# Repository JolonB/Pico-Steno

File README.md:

# Pico-Steno

An open-source Raspberry Pi Pico stenography keyboard.

I promise I'll write more here soon.

Gerber files can be found [here](hardware/gerber/).
I have not yet ordered a PCB with these gerber files, so they may have issues.

The bill of materials can be found [here](docs/bom/).

## Setup

### Flashing Pico

<!-- TODO add instructions for flashing the circuitpython firmware -->

To begin, you need to have `circup` installed so you can add libraries to your Pico.
Start by installing the dependencies:

```shell
sudo apt install -y git python3 python3-pip
```

And then install `circup`:

```shell
pip3 install --upgrade pip
pip3 install circup
```

You can update `circup` by running:

```shell
pip3 install --upgrade circup
```

Now, you can simply install the packages by plugging in your Pico which is running CircuitPython and running:

```shell
cd src/
circup install -r requirements.txt
```

### Compiling Code

To compile the code, you need `mpy-cross` installed on your PC.
You can download it from [here](https://adafruit-circuit-python.s3.amazonaws.com/index.html?prefix=bin/mpy-cross/) and download the latest version for your operating system (or look [here](https://learn.adafruit.com/welcome-to-circuitpython/frequently-asked-questions#how-can-i-create-my-own-mpy-files-3020687-11) if the link is dead).

<!-- TODO add more notes here
Probably only need to compile the custom code, not the libraries. Might as well use circup (https://learn.adafruit.com/keep-your-circuitpython-libraries-on-devices-up-to-date-with-circup/prepare)
Later, could add an explanation for how to build a whole circuit python firmware with custom lib?? -->

### Loading .mpy files onto Pico

## Questions

### Why doesn't this use a keyboard matrix?

Good question.

1. The RPi Pico has enough GPIO pins to dedicate one to each key on a stenography keyboard.
Basically, I just though that was neat, so decided to do it that way.
I then decided I wanted optional extra keys, so added the IO extender.
1. This allows me to implement n-key rollover without needing any diodes; not that they are particularly expensive.

### Why is the circuit so messy?

That's what happens when each key is connected directly to the microcontroller without optimising the which switch connects to which pin.  
But hey, this is open source; if it bugs you, feel free to fork it!

## I can't detect my board

```shell
pip3 install adafruit-board-toolkit
python3 -c "import adafruit_board_toolkit.circuitpython_serial; print(adafruit_board_toolkit.circuitpython_serial.data_comports()[0].device)"
```

If you get `IndexError: tuple index out of range`, then no data port was detected.

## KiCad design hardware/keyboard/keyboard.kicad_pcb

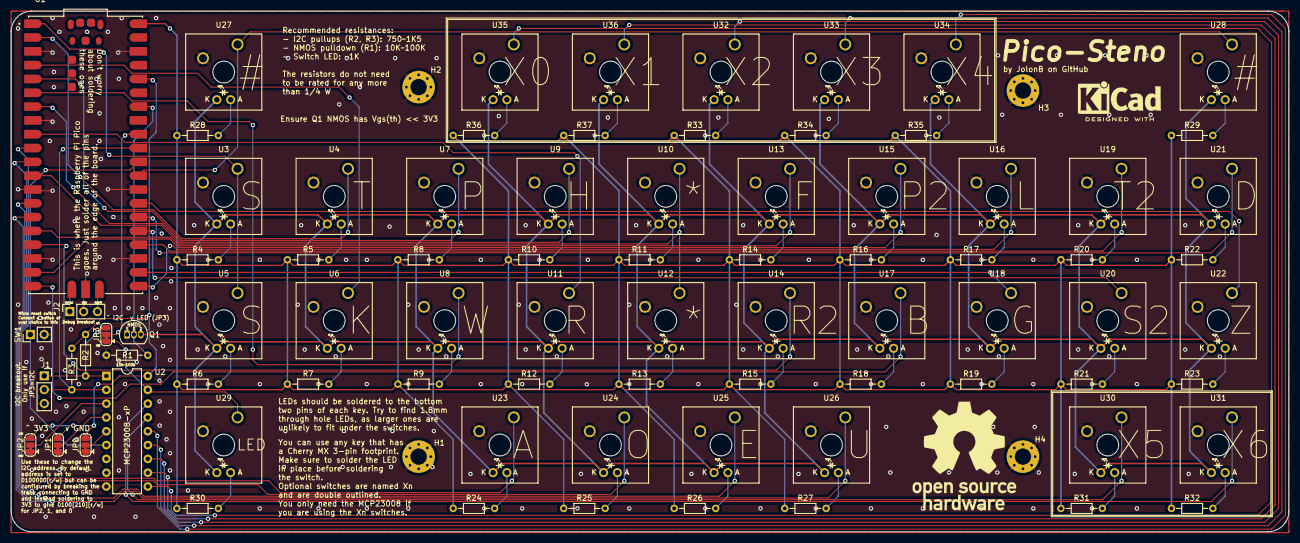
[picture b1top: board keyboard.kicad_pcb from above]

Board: 2 copper layers, 234.9 x 95.7 mm, 85 parts (0 on the bottom side), 79 nets.

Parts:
H1, H2, H3, H4: MountingHole_Pad; MountingHole_3mm_Pad_Via
J1, J2: Conn_01x03_Female; PinSocket_1x03_P2.54mm_Vertical
JP0, JP1, JP2, JP3: SolderJumper_3_Bridged12; SolderJumper-3_P1.3mm_Bridged12_RoundedPad1.0x1.5mm
Q1: Q_NMOS_SGD; TO-92L_Inline
R1, R2, R3, R4, R5, R6, R7, R8, R9, R10, R11, R12, R13, R14, R15, R16, R17, R18, R19, R20, R21, R22, R23, R24, R25, R26, R27, R28, R29, R30, R31, R32, R33, R34, R35, R36, R37: R; R_Axial_DIN0204_L3.6mm_D1.6mm_P7.62mm_Horizontal
SW1: SW_Push; PinHeader_1x02_P2.54mm_Vertical
U1: SC0915; MODULE_SC0915
U2: MCP23008-xP; DIP-18_W7.62mm
U3, U4, U5, U6, U7, U8, U9, U10, U11, U12, U13, U14, U15, U16, U17, U18, U19, U20, U21, U22, U23, U24, U25, U26, U27, U28, U29, U30, U31, U32, U33, U34, U35, U36: CherryMX_LED; CherryMX_1.00u_LED

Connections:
+3V3: JP0.3 (B), JP1.3 (B), JP2.3 (B), R2.1, R3.1, U1.36 (3V3_OUT), U2.18 (VDD)
+5V: R4.1, R5.1, R6.1, R7.1, R8.1, R9.1, R10.1, R11.1, R12.1, R13.1, R14.1, R15.1, R16.1, R17.1, R18.1, R19.1, R20.1, R21.1, R22.1, R23.1, R24.1, R25.1, R26.1, R27.1, R28.1, R29.1, R30.1, R31.1, R32.1, R33.1, R34.1, R35.1, R36.1, R37.1, U1.40 (VBUS)
/I2C_SCL: J1.1, JP3.3 (B), R2.2, U2.1 (SCL)
/I2C_SDA: J1.2, R3.2, U1.31 (GP26), U2.2 (SDA)
/IO_A0: JP0.2 (C), U2.5 (A0)
/IO_A1: JP1.2 (C), U2.4 (A1)
/IO_A2: JP2.2 (C), U2.3 (A2)
/KEY_A: U1.10 (GP7), U23.2
/KEY_B: U1.20 (GP15), U17.2
/KEY_D: U1.26 (GP20), U21.2
/KEY_E: U1.14 (GP10), U25.2
/KEY_EXT0: U2.10 (GP0), U35.2
/KEY_EXT1: U2.11 (GP1), U36.2
/KEY_EXT2: U2.12 (GP2), U32.2
/KEY_EXT3: U2.13 (GP3), U33.2
/KEY_EXT4: U2.14 (GP4), U34.2
/KEY_EXT5: U2.15 (GP5), U30.2
/KEY_EXT6: U2.16 (GP6), U31.2
/KEY_F: U1.16 (GP12), U13.2
/KEY_G: U1.22 (GP17), U18.2
/KEY_H: U1.7 (GP5), U9.2
/KEY_K: U1.4 (GP2), U6.2
/KEY_L: U1.21 (GP16), U16.2
/KEY_NUM: U1.29 (GP22), U27.2, U28.2
/KEY_O: U1.11 (GP8), U24.2
/KEY_P: U1.5 (GP3), U7.2
/KEY_P2: U1.19 (GP14), U15.2
/KEY_R: U1.9 (GP6), U11.2
/KEY_R2: U1.17 (GP13), U14.2
/KEY_S: U1.1 (GP0), U3.2, U5.2
/KEY_S2: U1.25 (GP19), U20.2
/KEY_STAR: U1.12 (GP9), U10.2, U12.2
/KEY_T: U1.2 (GP1), U4.2
/KEY_T2: U1.24 (GP18), U19.2
/KEY_U: U1.15 (GP11), U26.2
/KEY_W: U1.6 (GP4), U8.2
/KEY_Z: U1.27 (GP21), U22.2
/LED_CTRL: Q1.3 (D), U3.3 (K), U4.3 (K), U5.3 (K), U6.3 (K), U7.3 (K), U8.3 (K), U9.3 (K), U10.3 (K), U11.3 (K), U12.3 (K), U13.3 (K), U14.3 (K), U15.3 (K), U16.3 (K), U17.3 (K), U18.3 (K), U19.3 (K), U20.3 (K), U21.3 (K), U22.3 (K), U23.3 (K), U24.3 (K), U25.3 (K), U26.3 (K), U27.3 (K), U28.3 (K), U29.3 (K), U30.3 (K), U31.3 (K), U32.3 (K), U33.3 (K), U34.3 (K), U35.3 (K), U36.3 (K)
/LED_PWM: Q1.2 (G), R1.1, U1.34 (GP28)
/LED_SET: JP3.1 (A), U2.17 (GP7), U29.2
/RESET: SW1.1, U1.30 (~RUN), U2.6 (~RESET)
/SWCLK: J2.1, U1.D1 (SWCLK)
/SWDIO: J2.3, U1.D3 (SWDIO)
GND: H1.1, H2.1, H3.1, H4.1, J1.3, J2.2, JP0.1 (A), JP1.1 (A), JP2.1 (A), Q1.1 (S), R1.2, SW1.2, U1.3 (GND), U1.8 (GND), U1.13 (GND), U1.18 (GND), U1.23 (GND), U1.28 (GND), U1.38 (GND), U1.D2 (GND), U2.9 (VSS), U3.1, U4.1, U5.1, U6.1, U7.1, U8.1, U9.1, U10.1, U11.1, U12.1, U13.1, U14.1, U15.1, U16.1, U17.1, U18.1, U19.1, U20.1, U21.1, U22.1, U23.1, U24.1, U25.1, U26.1, U27.1, U28.1, U29.1, U30.1, U31.1, U32.1, U33.1, U34.1, U35.1, U36.1
unnamed: JP3.2 (C), U1.32 (GP27)
unnamed: R4.2, U3.4 (A)
unnamed: R5.2, U4.4 (A)
unnamed: R6.2, U5.4 (A)
unnamed: R7.2, U6.4 (A)
unnamed: R8.2, U7.4 (A)
unnamed: R9.2, U8.4 (A)
unnamed: R10.2, U9.4 (A)
unnamed: R11.2, U10.4 (A)
unnamed: R12.2, U11.4 (A)
unnamed: R13.2, U12.4 (A)
unnamed: R14.2, U13.4 (A)
unnamed: R15.2, U14.4 (A)
unnamed: R16.2, U15.4 (A)
unnamed: R17.2, U16.4 (A)
unnamed: R18.2, U17.4 (A)
unnamed: R19.2, U18.4 (A)
unnamed: R20.2, U19.4 (A)
unnamed: R21.2, U20.4 (A)
unnamed: R22.2, U21.4 (A)
unnamed: R23.2, U22.4 (A)
unnamed: R24.2, U23.4 (A)
unnamed: R25.2, U24.4 (A)
unnamed: R26.2, U25.4 (A)
unnamed: R27.2, U26.4 (A)
unnamed: R28.2, U27.4 (A)
unnamed: R29.2, U28.4 (A)
unnamed: R30.2, U29.4 (A)
unnamed: R31.2, U30.4 (A)
unnamed: R32.2, U31.4 (A)
unnamed: R33.2, U32.4 (A)
unnamed: R34.2, U33.4 (A)
unnamed: R35.2, U34.4 (A)
unnamed: R36.2, U35.4 (A)
unnamed: R37.2, U36.4 (A)

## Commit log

2022-07-26 Add initial keyboard design
2022-07-30 Add documentation to PCB
2022-07-30 Add BOM and images
2022-07-30 Create gerber files
2022-07-30 Add gerber PDFs
2022-07-31 Update I2C header
2022-07-31 Add mounting holes
2022-07-31 Add KiCad logo to PCB
2022-08-05 Setup src
2022-08-05 Add button library using asyncio
2022-08-06 Add backlight class
    Also improve the button class
2022-08-10 Add usb_cdc interface in TXBolt class
2022-09-04 Implement stenography keyboard
    Extra keys don't do anything yet though
2022-09-11 Add keycap model
